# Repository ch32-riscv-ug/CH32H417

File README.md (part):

# CH32H417

<!-- This file is generated from ch32-riscv-ug/ch32-device-data (index/ + evidence/ + pipeline/build/build_readme.py). Edit there, not here. -->

[Choose a part](#product-comparison) &middot; [Documents](#documents) &middot; [Pin maps](#pin-maps--alternate-functions) &middot; [Pin viewer](https://ch32-riscv-ug.github.io/ch32-device-data/pins.html?chip=CH32H415) &middot; [Errata](#errata) &middot; [Examples](#evt-examples) &middot; [Address map](#address-map)

## Quick start

### Debug / serial defaults

Where these land **without writing a remap register**. SWD is live at reset; the UART pads are not -- the pin must still be put into alternate-function mode. See `route` in evidence/README.ja.md.

| Series | SWDIO | SWCLK | UART TX | UART RX |
|---|---|---|---|---|
| CH32H415 | PB9 | PB8 | none by default[^af] | none by default[^af] |
| CH32H416 | PB9 | PB8 | none by default[^af] | none by default[^af] |
| CH32H417 | PB9 | PB8 | none by default[^af] | none by default[^af] |

[^af]: This series selects every pin function through `AFIO->GPIOx_AFLR/AFHR` rather than through AFIO remap, so no USART is routed out until software picks one -- the pads it **can** go on are listed under Pin definitions. The reset value of `GPIOx_AFLR/AFHR` is 0, which selects AF0 (a real function, not "none"), and a pad only drives its alternate function once its GPIO mode is set to alternate.

### Datasheets and reference manual

- CH32H417DS0.PDF (datasheet): [English](https://ch32-riscv-ug.github.io/CH32H417/datasheet_en/CH32H417DS0.PDF) · [中文](https://ch32-riscv-ug.github.io/CH32H417/datasheet_zh/CH32H417DS0.PDF)
- CH32H417RM.PDF (reference manual): [English](https://ch32-riscv-ug.github.io/CH32H417/datasheet_en/CH32H417RM.PDF) · [中文](https://ch32-riscv-ug.github.io/CH32H417/datasheet_zh/CH32H417RM.PDF)

## Series

| Series | Core | ISA | Flash | SRAM | Main clock | VDD | Packages | Products | Official |
|---|---|---|---|---|---|---|---|---|---|
| **CH32H415** | QingKe V5F + QingKe V3F | RV32IMABCF + RV32IMAFCB | 960K | 896K | 160 MHz\* | - | QFN60X6 | 1 | [en](https://www.wch-ic.com/products/CH32H415.html) / [zh](https://www.wch.cn/products/CH32H415.html) |
| **CH32H416** | QingKe V5F + QingKe V3F | RV32IMABCF + RV32IMAFCB | 480K | 896K | 160 MHz\* | - | QFN60X6 | 1 | [en](https://www.wch-ic.com/products/CH32H416.html) / [zh](https://www.wch.cn/products/CH32H416.html) |
| **CH32H417** | QingKe V5F + QingKe V3F | RV32IMABCF + RV32IMAFCB | 960K | 896K | 160 MHz\* | - | QFN128,QFN68,QFN88 | 3 | [en](https://www.wch-ic.com/products/CH32H417.html) / [zh](https://www.wch.cn/products/CH32H417.html) |

\* the datasheet states no nominal system main frequency for this series, so the figure is the electrical maximum (HCLK) from the characteristics table -- a limit, not a rating.

## Product comparison

### CH32H417 product comparison

Only the 15 rows that differ between these 3 products; the other 32 are the same for all of them.

| | [CH32H417&#8203;MEU6](https://ch32-riscv-ug.github.io/ch32-device-data/pins.html?chip=CH32H417MEU6)&#8203;(QFN88) | [CH32H417&#8203;QEU6](https://ch32-riscv-ug.github.io/ch32-device-data/pins.html?chip=CH32H417QEU6)&#8203;(QFN128) | [CH32H417&#8203;WEU6](https://ch32-riscv-ug.github.io/ch32-device-data/pins.html?chip=CH32H417WEU6)&#8203;(QFN68) |
|---|---|---|---|
| **GPIO** | 65 | 95 | 50 |
| ADC/TKey Channels | 9+2 | 16+2 | 7+2 |
| HSADC Channels | 4 | 7 | 4 |
| DAC (Unit) | 2 | 2 | 1 (DAC2) |
| OPA | 2(OPA1/3) | 3 | 1(OPA1) |
| USART | 8 | 8 | 7 |
| SPI/I2S | 4/2 | 4/2 | 3/2 |
| QSPI | 1 (QSPI2) | 2 | 1 (QSPI2) |
| UHSIF | 1 | 1 | 1(1) |
| SDIO | - | 1 | - |
| USBFS/OTG_FS | 1 | 1 | - |
| USBPD Type-C | 1 | 1 | - |
| FSMC | 1(2) | 1 | 1(2) |
| SerDes | 1 | 1 | - |
| SDRAM | 1 | 1 | 1(3) |

<details><summary>All 47 rows</summary>

| | [CH32H417&#8203;MEU6](https://ch32-riscv-ug.github.io/ch32-device-data/pins.html?chip=CH32H417MEU6)&#8203;(QFN88) | [CH32H417&#8203;QEU6](https://ch32-riscv-ug.github.io/ch32-device-data/pins.html?chip=CH32H417QEU6)&#8203;(QFN128) | [CH32H417&#8203;WEU6](https://ch32-riscv-ug.github.io/ch32-device-data/pins.html?chip=CH32H417WEU6)&#8203;(QFN68) |
|---|---|---|---|
| **Flash** | 960K | 960K | 960K |
| **SRAM** | 896K | 896K | 896K |
| **GPIO** | 65 | 95 | 50 |
| **Temperature** | -40..85C | -40..85C | -40..85C |
| Core 1 HS ITCM | 128KB | 128KB | 128KB |
| Core 1 HS DTCM | 256KB | 256KB | 256KB |
| SRAM Shared code and data area | 512KB | 512KB | 512KB |
| ADTM (16-bit) | 2 | 2 | 2 |
| GPTM (16-bit) | 4 | 4 | 4 |
| GPTM (32-bit) | 4 | 4 | 4 |
| Basic (16-bit) | 2 | 2 | 2 |
| LPTIM | 2 | 2 | 2 |
| Timer Watchdog | WWDG+IWDG | WWDG+IWDG | WWDG+IWDG |
| SysTick 32-bit | 2 | 2 | 2 |
| RTC | √ | √ | √ |
| ADC/TKey Units | 2 | 2 | 2 |
| ADC/TKey Channels | 9+2 | 16+2 | 7+2 |
| HSADC Units | 1 | 1 | 1 |
| HSADC Channels | 4 | 7 | 4 |
| DAC (Unit) | 2 | 2 | 1 (DAC2) |
| OPA | 2(OPA1/3) | 3 | 1(OPA1) |
| CMP | 1 | 1 | 1 |
| DFSDM | 1 | 1 | 1 |
| RNG | 1 | 1 | 1 |
| LTDC | 1 | 1 | 1 |
| GPHA | 1 | 1 | 1 |
| DVP | 1 | 1 | 1 |
| USART | 8 | 8 | 7 |
| SPI/I2S | 4/2 | 4/2 | 3/2 |
| QSPI | 1 (QSPI2) | 2 | 1 (QSPI2) |
| I2C | 4 | 4 | 4 |
| I3C | 1 | 1 | 1 |
| UHSIF | 1 | 1 | 1(1) |
| CAN | 3 | 3 | 3 |
| SDMMC | 1 | 1 | 1 |
| SDIO | - | 1 | - |
| SAI | 1 | 1 | 1 |
| SWPMI | 1 | 1 | 1 |
| USBFS/OTG_FS | 1 | 1 | - |
| USBHS (USB2.0) | 1 | 1 | 1 |
| USBSS (USB3.0) | 1 | 1 | 1 |
| Ethernet | MAC+10/100M PHY | MAC+10/100M PHY | MAC+10/100M PHY |
| USBPD Type-C | 1 | 1 | - |
| FSMC | 1(2) | 1 | 1(2) |
| SerDes | 1 | 1 | - |
| SDRAM | 1 | 1 | 1(3) |
| PIOC | 1 | 1 | 1 |

</details>

## Block diagrams

### CH32H415

<details><summary>Internal block diagram (datasheet)</summary>

</details>

### CH32H416

<details><summary>Internal block diagram (datasheet)</summary>

</details>

### CH32H417

System block diagram from the [WCH product page](https://www.wch-ic.com/products/CH32H417.html).

<details><summary>Internal block diagram (datasheet)</summary>

</details>

## Documents

| Document | Kind | English | 中文 |
|---|---|---|---|
| CH32H417DS0.PDF | datasheet | [page](https://www.wch-ic.com/downloads/CH32H417DS0_PDF.html) [mirror](https://ch32-riscv-ug.github.io/CH32H417/datasheet_en/CH32H417DS0.PDF) v1.9 | [page](https://www.wch.cn/downloads/CH32H417DS0_PDF.html) [mirror](https://ch32-riscv-ug.github.io/CH32H417/datasheet_zh/CH32H417DS0.PDF) v1.9 |
| CH32H417RM.PDF | reference-manual | [page](https://www.wch-ic.com/downloads/CH32H417RM_PDF.html) [mirror](https://ch32-riscv-ug.github.io/CH32H417/datasheet_en/CH32H417RM.PDF) v1.8 | [page](https://www.wch.cn/downloads/CH32H417RM_PDF.html) [mirror](https://ch32-riscv-ug.github.io/CH32H417/datasheet_zh/CH32H417RM.PDF) v1.8 |
| CH32H417EVT.ZIP | evt | [page](https://www.wch-ic.com/downloads/CH32H417EVT_ZIP.html) [mirror](https://github.com/ch32-riscv-ug/CH32H417/tree/main/EVT) v1.3 | [page](https://www.wch.cn/downloads/CH32H417EVT_ZIP.html) [mirror](https://github.com/ch32-riscv-ug/CH32H417/tree/main/EVT) v1.8 |

### Evaluation boards

- board-manual:en: [CH32H417 Evaluation Board Reference-EN.pdf](https://ch32-riscv-ug.github.io/CH32H417/EVT/PUB/CH32H417%20Evaluation%20Board%20Reference-EN.pdf)
- board-manual:zh: [CH32H417评估板说明书.pdf](https://ch32-riscv-ug.github.io/CH32H417/EVT/PUB/CH32H417%E8%AF%84%E4%BC%B0%E6%9D%BF%E8%AF%B4%E6%98%8E%E4%B9%A6.pdf)
- schematic-pdf: [CH32H417SCH.pdf](https://ch32-riscv-ug.github.io/CH32H417/EVT/PUB/CH32H417SCH.pdf)

7 board schematics under `EVT/PUB/SCHPCB/`: `CH32H415REU6-R0`, `CH32H416RDU6-R0`, `CH32H417MEU6-R0`, `CH32H417MEU6-UHSIF-R0`, `CH32H417QEU-R1`, `CH32H417QEU6-R0`, `CH32H417WEU6-R0`

## Packages & pinout drawings

Pinout drawings are in the datasheet (chapter *Pinouts*); each link opens at the page that carries the drawing:

| Package | Products | Datasheet | Outline |
|---|---|---|---|
| QFN60X6 | CH32H415REU6 | [en](https://ch32-riscv-ug.github.io/CH32H417/datasheet_en/CH32H417DS0.PDF#page=33) / [zh](https://ch32-riscv-ug.github.io/CH32H417/datasheet_zh/CH32H417DS0.PDF#page=26) | [drawing](https://raw.githubusercontent.com/ch32-riscv-ug/WCH-common/main/image/package_QFN60X6.png) |
| QFN60X6 | CH32H416RDU6 | [en](https://ch32-riscv-ug.github.io/CH32H417/datasheet_en/CH32H417DS0.PDF#page=32) / [zh](https://ch32-riscv-ug.github.io/CH32H417/datasheet_zh/CH32H417DS0.PDF#page=26) | [drawing](https://raw.githubusercontent.com/ch32-riscv-ug/WCH-common/main/image/package_QFN60X6.png) |
| QFN88 | CH32H417MEU6 | [en](https://ch32-riscv-ug.github.io/CH32H417/datasheet_en/CH32H417DS0.PDF#page=30) / [zh](https://ch32-riscv-ug.github.io/CH32H417/datasheet_zh/CH32H417DS0.PDF#page=25) | [drawing](https://raw.githubusercontent.com/ch32-riscv-ug/WCH-common/main/image/package_QFN88.png) |
| QFN128 | CH32H417QEU6 | [en](https://ch32-riscv-ug.github.io/CH32H417/datasheet_en/CH32H417DS0.PDF#page=29) / [zh](https://ch32-riscv-ug.github.io/CH32H417/datasheet_zh/CH32H417DS0.PDF#page=24) | [drawing](https://raw.githubusercontent.com/ch32-riscv-ug/WCH-common/main/image/package_QFN128.png) |
| QFN68 | CH32H417WEU6 | [en](https://ch32-riscv-ug.github.io/CH32H417/datasheet_en/CH32H417DS0.PDF#page=31) / [zh](https://ch32-riscv-ug.github.io/CH32H417/datasheet_zh/CH32H417DS0.PDF#page=25) | [drawing](https://raw.githubusercontent.com/ch32-riscv-ug/WCH-common/main/image/package_QFN68.png) |

## Pin maps & alternate functions

> [!NOTE]
> These are the **pin-table superset**: the datasheet prints one pad table for every product that shares a pinout, so a pad row does not mean this part has the peripheral. Use the product comparison table above for what a given part number contains.

### CH32H415 pin map

Pin functions (filterable): [ALL](https://ch32-riscv-ug.github.io/ch32-device-data/pins.html?chip=CH32H415) [ADC](https://ch32-riscv-ug.github.io/ch32-device-data/pins.html?chip=CH32H415&features=ADC) [I2C](https://ch32-riscv-ug.github.io/ch32-device-data/pins.html?chip=CH32H415&features=I2C) [SPI](https://ch32-riscv-ug.github.io/ch32-device-data/pins.html?chip=CH32H415&features=SPI) [SYS](https://ch32-riscv-ug.github.io/ch32-device-data/pins.html?chip=CH32H415&features=SYS) [TIM](https://ch32-riscv-ug.github.io/ch32-device-data/pins.html?chip=CH32H415&features=TIM) [UART](https://ch32-riscv-ug.github.io/ch32-device-data/pins.html?chip=CH32H415&features=UART) [USB](https://ch32-riscv-ug.github.io/ch32-device-data/pins.html?chip=CH32H415&features=USB)

<details><summary><b>CH32H415 pin map</b> (61 pads x 1 products)</summary>

| Pin name | Type | [CH32H415&#8203;REU6](https://ch32-riscv-ug.github.io/ch32-device-data/pins.html?chip=CH32H415REU6)&#8203;(QFN60X6) | Notes |
|---|---|---|---|
| PA0 | I/O/A | 14 |  |
| PA1 | I/O/A | 15 |  |
| PA2 | I/O/A | 16 |  |
| PA3 | I/O/A | 17 |  |
| PA4 | I/O/A | 18 |  |
| PA5 | I/O/A | 19 |  |
| PA6 | I/O/A | 20 |  |
| PA7 | I/O/A | 21 |  |
| PA9 | I/O/A | 40 |  |
| PA10 | I/O/A | 41 |  |
| PA11 | I/O/A | 42 |  |
| PA12 | I/O/A | 43 |  |
| PA13 | I/O | 44 |  |
| PA14 | I/O | 45 |  |
| PA15 | I/O | 46 |  |
| PB0 | I/O/A | 23 |  |
| PB1 | I/O/A | 24 |  |
| PB3 | I/O | 55 |  |
| PB4 | I/O | 56 |  |
| PB6 | I/O | 57 |  |
| PB7 | I/O | 58 |  |
| PB8 | I/O/A | 59 | SWCLK |
| PB9 | I/O/A | 60 | SWDIO |
| PB10 | I/O | 29 |  |
| PB11 | I/O | 30 |  |
| PB12 | I/O | 32 |  |
| PB13 | I/O | 33 |  |
| PB14 | I/O | 34 |  |
| PB15 | I/O | 35 |  |
| PC0 | I/O/A | 9 |  |
| PC1 | I/O/A | 10 |  |
| PC2 | I/O/A | 11 |  |
| PC3 | I/O/A | 12 |  |
| PC4 | I/O/A | 22 |  |
| PC6 | I/O | 36 |  |
| PC7 | I/O | 37 |  |
| PC8 | I/O | 38 |  |
| PC9 | I/O | 39 |  |
| PC10 | I/O | 47 |  |
| PC11 | I/O | 48 |  |
| PC12 | I/O | 49 |  |
| PD3 | I/O | 50 |  |
| PE0 | I/O | 54 |  |
| PE3 | I/O | 1 |  |
| PE4 | I/O | 2 |  |
| PE5 | I/O | 3 |  |
| PE6 | I/O | 4 |  |
| PE11 | I/O | 25 |  |
| PE12 | I/O | 26 |  |
| PE13 | I/O | 27 |  |
| PE14 | I/O | 28 |  |
| PE15 | I/O | 29 |  |
| PF3 | I/O | 51 |  |
| PF4 | I/O | 52 |  |
| PF5 | I/O | 53 |  |
| VDD33 | P | 6/31 |  |
| VDD33A | P | 13 |  |
| VDDK | P | 5 |  |
| VSS | P | EP |  |
| XI | I/A | 7 |  |
| XO | O/A | 8 |  |

</details>

<details><summary><b>CH32H415 alternate functions</b></summary>

| Pad | default | af-0 | af-1 | af-10 | af-11 | af-12 | af-13 | af-14 | af-15 | af-2 | af-3 | af-4 | af-5 | af-6 | af-7 | af-8 | af-9 |
|---|---|---|---|---|---|---|---|---|---|---|---|---|---|---|---|---|---|
| PA0 | ADC_IN0, OPA3_OUT0 | - | TIM2_CH1_ETR | - | - | - | - | LTDC_R0 | - | TIM5_CH1 | TIM8_ETR | QSPI2_SIOX2 | PIOC_IO0 | TIM9_CH1 | USART2_CTS | USART6_TX | SDIO_CMD |
| PA1 | ADC_IN1 | - | TIM2_CH2 | - | - | - | - | LTDC_R2 | - | TIM5_CH2 | - | QSPI2_SIOX3 | - | TIM9_CH2 | USART2_RTS | USART6_RX | QSPI1_SIO3 |
| PA2 | ADC_IN2, OPA3_P1 | - | TIM2_CH3 | - | - | - | - | LTDC_R1 | - | TIM5_CH3 | USART6_CK | TIM9_CH3 | - | - | USART2_TX | - | - |
| PA3 | ADC_IN3, OPA3_N1 | - | TIM2_CH4 | - | - | - | - | LTDC_B5 | - | TIM5_CH4 | - | TIM9_CH4 | - | - | USART2_RX | TIM10_CH3 | LTDC_B2 |
| PA4 | ADC_IN4, DAC1_OUT, OPA3_OUT1 | - | - | - | - | - | DVP_HSYNC | LTDC_VSYNC | - | TIM5_ETR | - | TIM9_ETR | SPI1_NSS | I2S3_WS, SPI3_NSS | USART2_CK | - | TIM10_CH4 |
| PA5 | ADC_IN5, DAC2_OUT, OPA1_OUT1 | - | TIM2_CH1_ETR | - | DVP_VSYNC | - | - | LTDC_R4 | - | TIM1_BKIN2 | TIM8_CH1N | - | SPI1_SCK | - | - | - | TIM10_ETR |
| PA6 | ADC_IN6, OPA1_P1 | - | TIM1_BKIN | CMP_OUT | LTDC_HSYNC | - | DVP_PCLK | LTDC_G2 | - | TIM3_CH1 | TIM8_BKIN | - | SPI1_MISO | - | - | - | TIM10_CH1 |
| PA7 | ADC_IN7, OPA1_N1 | - | TIM1_CH1N | - | - | - | - | LTDC_VSYNC | - | TIM3_CH2 | TIM8_CH1N | - | SPI1_MOSI | - | - | - | TIM10_CH2 |
| PA9 | OTG_VBUS | - | TIM1_CH2 | - | - | - | DVP_D0 | LTDC_R5 | - | - | - | I2C3_SMBA | I2S2_CK, SPI2_SCK | - | USART1_TX | - | - |
| PA10 | OTG_ID | - | TIM1_CH3 | - | - | LTDC_B4 | DVP_D1 | LTDC_B1 | - | - | - | - | - | USART6_CK | USART1_RX | - | - |
| PA11 | OTG_DM | - | TIM1_CH4 | - | - | - | - | LTDC_R4 | - | - | - | USART3_CK | I2S2_WS, SPI2_NSS | USART6_RX | USART1_CTS | - | CAN1_RX |
| PA12 | OTG_DP | - | TIM1_ETR | - | - | TIM1_BKIN2 | - | LTDC_R5 | - | - | - | USART3_RTS | I2S2_CK, SPI2_SCK | USART6_TX | USART1_RTS | - | CAN1_TX |
| PA13 | - | - | I2S3_SD, SPI3_MOSI | - | - | - | SAI_SD_B | - | - | - | - | USART3_TX | CAN_RX | - | I2C3_SDA | LTDC_B2 | - |
| PA14 | - | - | I2S3_CK, SPI3_SCK | - | USART8_CK | - | SAI_SCK_B | LTDC_B6 | LTDC_R0 | - | - | USART3_RX | CAN_TX | - | I2C3_SCL | - | - |
| PA15 | - | - | TIM2_CH1_ETR | LTDC_B4 | USART8_TX | - | SAI_FS_B | LTDC_B6 | LTDC_CLK | - | - | USART3_CTS | SPI1_NSS | I2S3_WS, SPI3_NSS | I2C3_SMBA | USART6_RTS | LTDC_R3 |
| PB0 | ADC_IN8, CMP_P0, OPA1_P0 | MCO | TIM1_CH2N | - | - | - | TIM12_ETR | LTDC_G1 | - | TIM3_CH3 | TIM8_CH2N | TIM5_CH4 | - | DFSDM_CKOUT | - | USART6_CTS | LTDC_R3 |
| PB1 | ADC_IN9, CMP_N0, OPA1_N0 | - | TIM1_CH3N | - | - | - | - | LTDC_G0 | - | TIM3_CH4 | TIM8_CH3N | - | TIM12_CH1 | DFSDM_DATIN1 | - | - | LTDC_R6 |
| PB3 | - | - | TIM2_CH2 | - | USART8_RX | - | DVP_D5 | TIM12_ETR | - | - | - | CC1 | SPI1_SCK | I2S3_CK, SPI3_SCK | - | - | SDIO_D2 |
| PB4 | - | - | - | TIM4_ETR | USART8_TX | - | - | USART7_CK | - | TIM3_CH1 | - | CC2 | SPI1_MISO | SPI3_MISO | I2S2_WS, SPI2_NSS | - | SDIO_D3 |
| PB6 | - | TIM10_CH1 | - | QSPI1_SCSN | - | - | DVP_D5 | USART7_TX | - | TIM4_CH1 | CAN1_RX | I2C1_SCL | I2S3_MCK | I2C4_SCL | USART1_TX | - | CAN2_TX |
| PB7 | - | TIM10_CH2 | - | USART8_CK | - | - | DVP_VSYNC | - | - | TIM4_CH2 | CAN1_TX | I2C1_SDA | - | I2C4_SDA | USART1_RX | - | - |
| PB8 | SWCLK, USBHS_DP | - | TIM10_CH3 | SDIO_D4 | - | - | DVP_D6 | LTDC_B6 | - | TIM4_CH3 | - | I2C1_SCL | PIOC_IO0 | I2C4_SCL | - | USART6_RX | CAN1_RX |
| PB9 | SWDIO, SWIO, USBHS_DM | - | TIM10_CH4 | SDIO_D5 | I2C4_SMBA | - | DVP_D7 | LTDC_B7 | - | TIM4_CH4 | - | I2C1_SDA | I2S2_WS, SPI2_NSS | I2C4_SDA | PIOC_IO1 | USART6_TX | CAN1_TX |
| PB10 | - | - | TIM2_CH3 | - | QSPI2_SCSXN | - | - | LTDC_G4 | - | TIM9_CH2 | LPTIM2_CH1 | I2C2_SCL | I2S2_CK, SPI2_SCK | - | USART3_TX | SDIO_CMD | USART6_CK |
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
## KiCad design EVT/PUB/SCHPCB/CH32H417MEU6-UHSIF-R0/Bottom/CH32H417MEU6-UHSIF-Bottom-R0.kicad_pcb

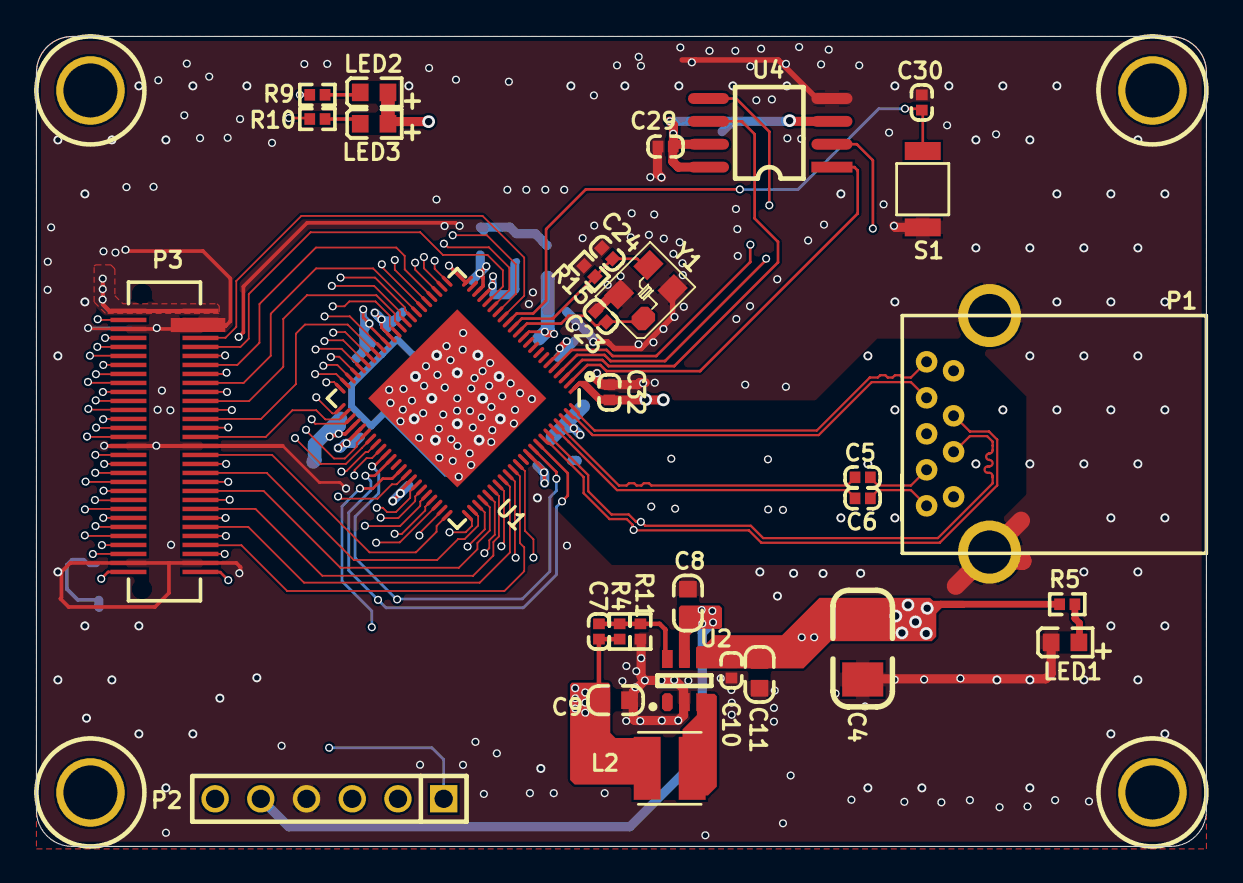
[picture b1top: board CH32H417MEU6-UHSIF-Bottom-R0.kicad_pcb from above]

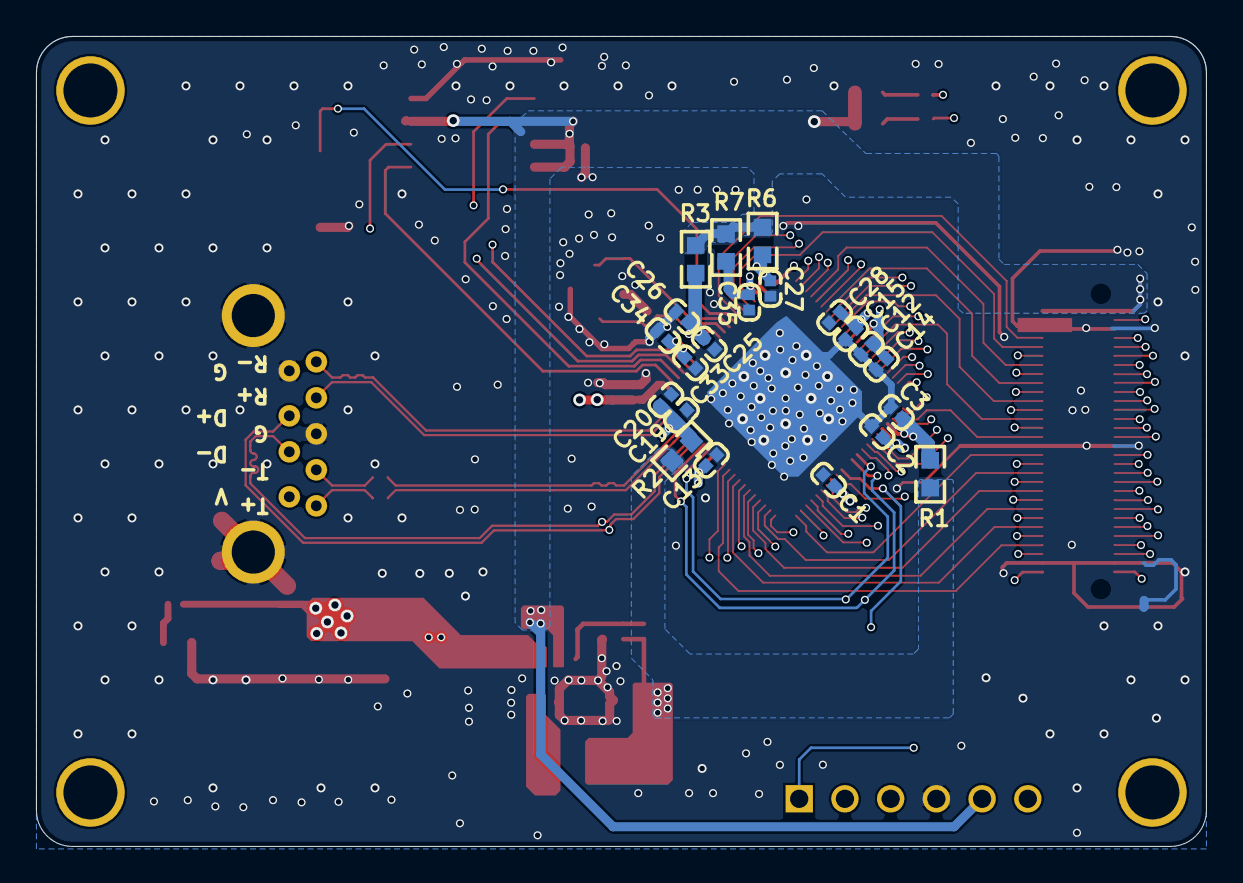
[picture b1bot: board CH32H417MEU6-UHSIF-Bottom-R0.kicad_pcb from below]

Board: 4 copper layers, 65.0 x 45.0 mm, 52 parts (21 on the bottom side), 84 nets.

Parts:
C1, C2, C3, C5, C6, C12, C13, C15, C19, C25, C27, C29, C30, C32, C33, C35: 0.1uF; 0402_C
C4: 47uF; 3528_C
C7: NC(4.7pF); 0402_C
C8, C9, C11: 10uF; 0603_C
C10: 1uF; 0402_C
C14, C26: 10uF; 0402_C
C20, C28, C34: 2.2uF; 0402_C
C23, C24: 20pF; 0402_C
L2: 2.2uH; CD32
LED1: RED; 0603+
LED2: BLUE; 0603+
LED3: GREEN; 0603+
P1: USB3.0-A; USB3.0-A-RECEPTACLE
P2: HEADER 6; SIP6-2.54mm
P3: HEADER 30x2; BTB-60P-P0.5-MR
R1, R2, R3, R6, R7: 0R; 0603
R4: 0Ω; 0402
R5: 1K; 0402
R9, R10: 470Ω; 0402
R11: NC(200k); 0402
R15: NC; 0402
S1: 贴片按键
U1: CH32H417MEU6; QFN88_10X10
U2: CH2003V; SOT-23-6
U4: SPI FLASH; SOIC-8_208mil
Y1: 25M; XT3225

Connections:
1V2: C7.1, C9.2, L2.2, R1.2, R2.2, R4.1
3V3: C8.2, C29.2, LED2.1, LED3.1, P2.5, P3.1, P3.2, R3.2, R6.2, R7.2, U2.5, U4.3, U4.7, U4.8
+5V: C4.1, C10.2, C11.2, P1.1, P2.6, R5.2, U2.4
GND: C1.2, C2.2, C3.1, C4.2, C8.1, C9.1, C10.1, C11.1, C12.2, C13.2, C14.2, C15.1, C19.1, C20.1, C23.1, C24.1, C25.1, C26.1, C27.1, C28.1, C29.1, C30.1, C32.1, C33.1, C34.1, C35.1, LED1.2, P1.0, P1.4, P1.7, P2.4, P3.4, P3.5, P3.6, P3.31, P3.32, P3.57, P3.58, R11.2, R15.1, S1.2, U1.0, U2.2, U4.4, Y1.2, Y1.4
LED1: R9.1, U1.22
LED2: R10.1, U1.23
NRST: C30.2, S1.1, U1.14
NetC5_2: C5.2, P1.8
NetC6_2: C6.2, P1.9
NetC7_2: C7.2, R4.2, R11.1, U2.6
NetL2_1: L2.1, U2.3
NetLED1_1: LED1.1, R5.1
NetLED2_2: LED2.2, R9.2
NetLED3_2: LED3.2, R10.2
RX1: P3.60, U1.55, U1.81
RX8: P3.59, U1.54, U1.80
SPI_CS: U1.2, U4.1
SPI_MISO: U1.4, U4.2
SPI_MOSI: U1.5, U4.5
SPI_SCK: U1.3, U4.6
SWCLK: P1.3, P2.2, U1.82
SWDIO: P1.2, P2.3, U1.83
TX6: P2.1, U1.57
UFP0: P3.3, U1.16
UFP1: P3.7, U1.17
UFP2: P3.10, U1.18
UFP3: P3.9, U1.24
UFP4: P3.12, U1.25
UFP5: P3.14, U1.26
UFP6: P3.11, U1.27
UFP7: P3.13, U1.28
UFP8: P3.18, U1.29
UFP9: P3.15, U1.30
UFP10: P3.16, U1.31
UFP11: P3.22, U1.32
UFP12: P3.17, U1.33
UFP13: P3.19, U1.36
UFP14: P3.26, U1.37
UFP15: P3.21, U1.38
UFP16: P3.20, U1.39
UFP17: P3.25, U1.40
UFP18: P3.23, U1.41
UFP19: P3.24, U1.42
UFP20: P3.27, U1.43
UFP21: P3.28, U1.44
UFP22: P3.29, U1.45
UFP23: P3.30, U1.46
UFP24: P3.33, U1.47
UFP25: P3.35, U1.50
UFP26: P3.37, U1.51
UFP27: P3.39, U1.52
UFP28: P3.41, U1.53
UFP29: P3.43, U1.58
UFP30: P3.45, U1.60
UFP31: P3.47, U1.61
UFP32: P3.49, U1.62
UFP33: P3.51, U1.63
UFP34: P3.53, U1.64
UFP35: P3.55, U1.65
UFP36: P3.34, U1.66
UFP37: P3.36, U1.67
UFP38: P3.38, U1.68
UFP39: P3.40, U1.69
UFP40: P3.42, U1.70
UFP41: P3.44, U1.71
UFP42: P3.46, U1.72
UFP43: P3.48, U1.73
UFP44: P3.50, U1.74
UFP45: P3.52, U1.75
UFP46: P3.54, U1.76
UFP47: P3.56, U1.77
UFPCLK: P3.8, U1.15
USB_SSRX_n: P1.6, U1.87
USB_SSRX_p: P1.5, U1.88
USB_SSTX_n: C6.1, U1.84
USB_SSTX_p: C5.1, U1.85
VDD12A: C19.2, C20.2, R2.1, U1.86
VDD33: C1.1, C25.2, C26.2, C32.2, R3.1, U1.1, U1.11, U1.59
VDD33A: C27.2, R6.1, U1.20
VDDIO: C12.1, C14.1, C35.2, R7.1, U1.19, U1.35
VDDK: C3.2, C33.2, C34.2, R1.1, U1.6, U1.48
VIO18: C2.1, C13.1, C15.2, C28.2, U1.34, U1.49, U1.79
XI: C23.2, U1.12, Y1.1
XO: C24.2, R15.2, U1.13, Y1.3

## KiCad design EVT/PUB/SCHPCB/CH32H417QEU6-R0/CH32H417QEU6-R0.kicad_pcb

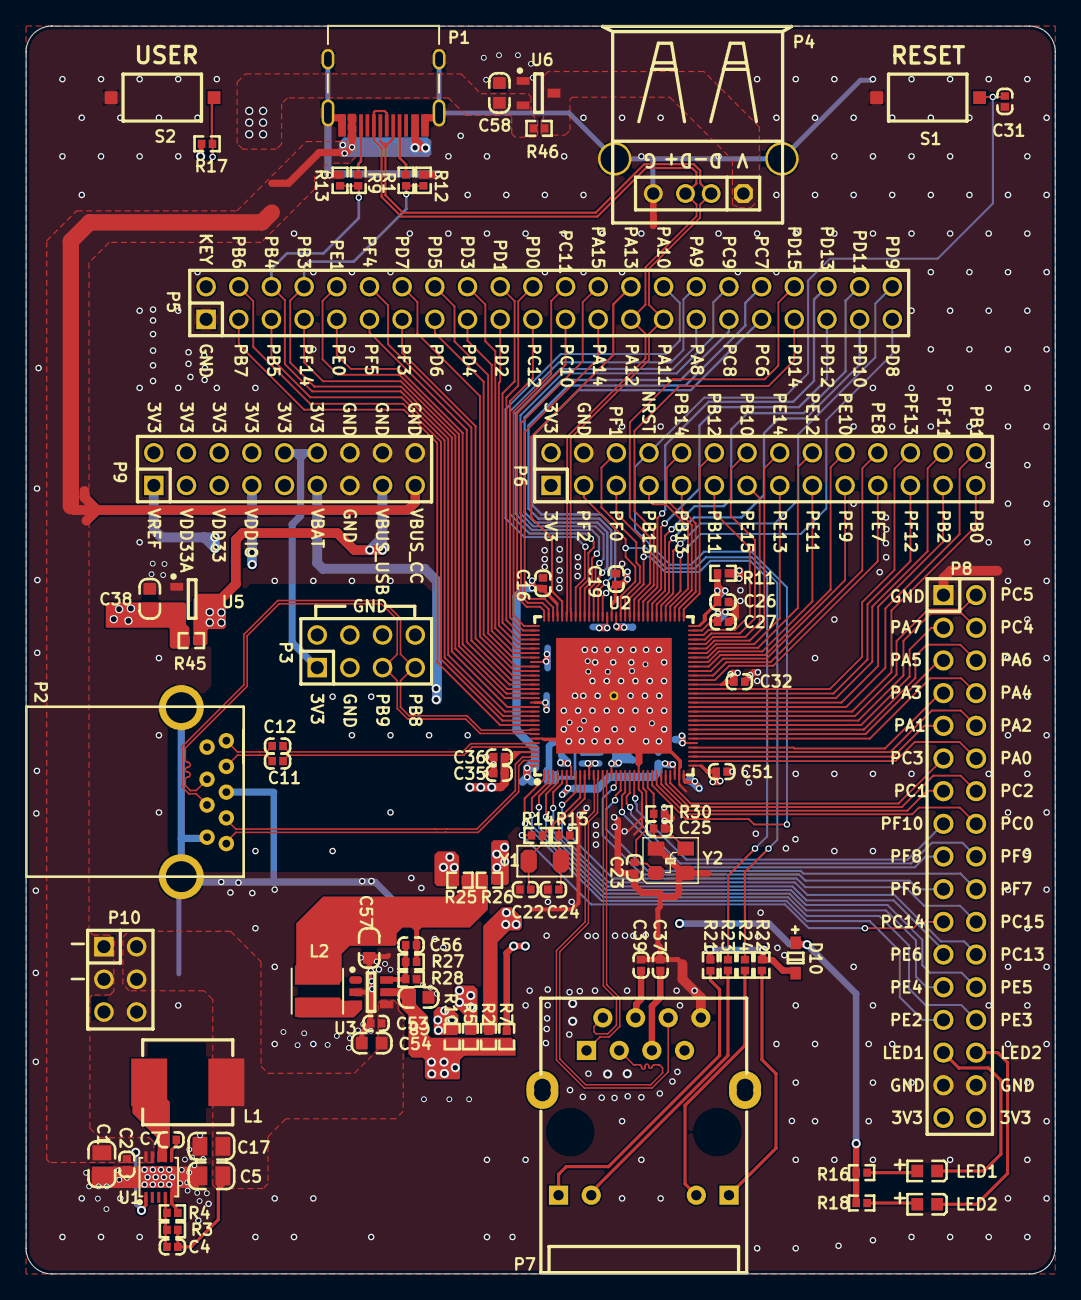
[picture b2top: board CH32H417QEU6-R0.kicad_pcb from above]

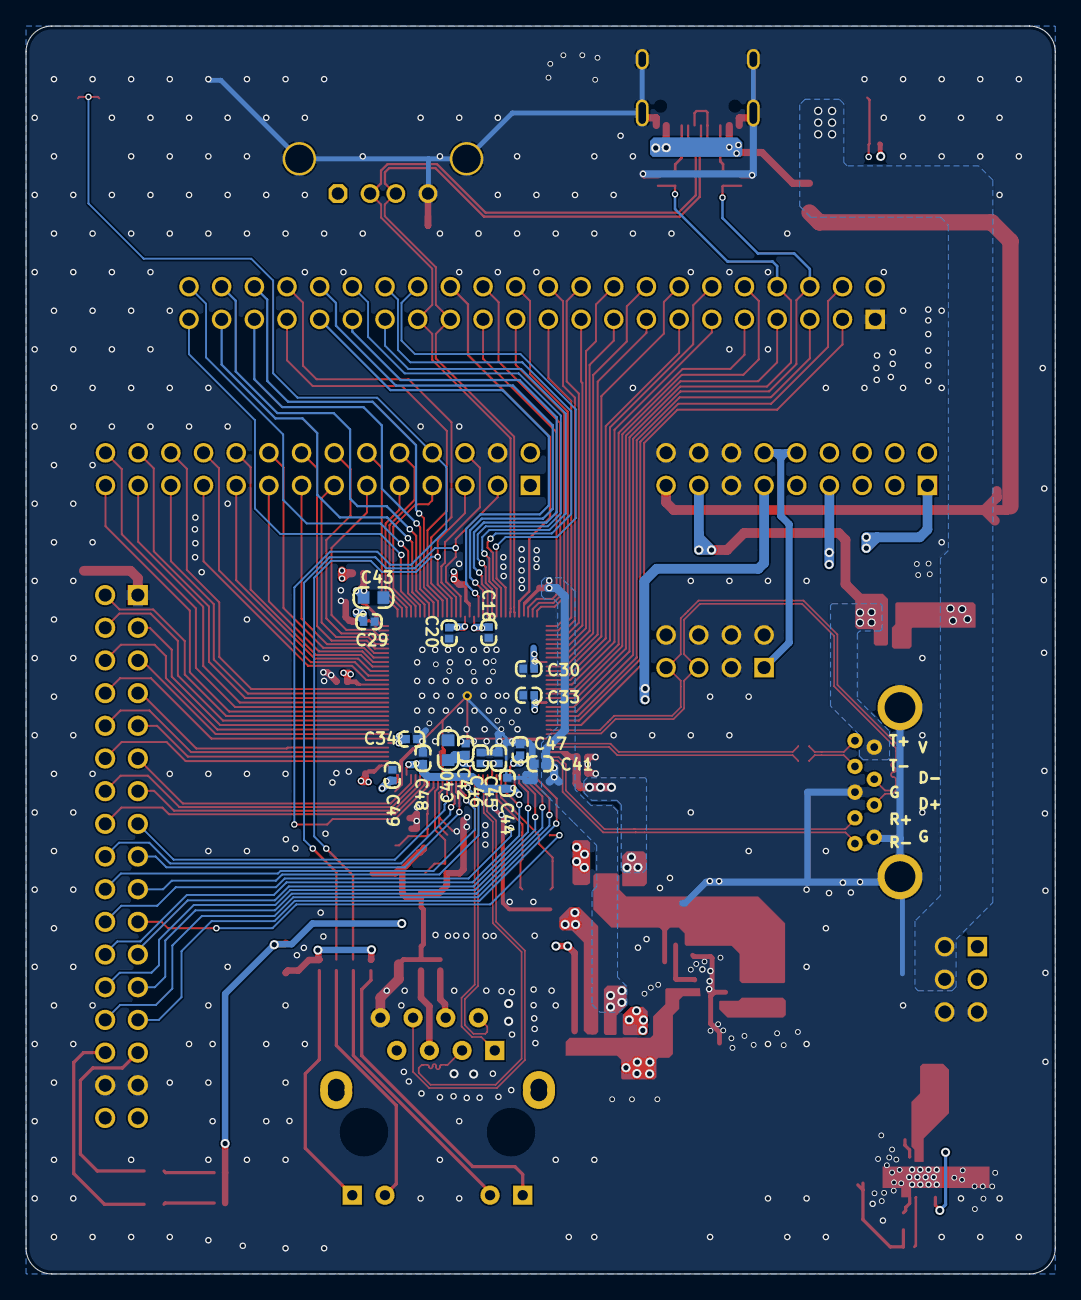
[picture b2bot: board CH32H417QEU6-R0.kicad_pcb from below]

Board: 4 copper layers, 80.0 x 97.0 mm, 97 parts (16 on the bottom side), 144 nets.

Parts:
C1: NC(22uF/35V); 0805_C
C2: NC(0.1uF); 0402_C
C4: NC(68pF); 0402_C
C5, C17: NC(22uF); 0805_C
C7: NC(100nF); 0402_C
C8, C38, C40, C43, C54, C58: 10uF; 0603_C
C11, C12, C16, C18, C19, C20, C26, C27, C30, C31, C32, C33, C34, C36, C37, C39, C41, C42, C44, C45, C47, C48, C49, C51: 0.1uF; 0402_C
C22, C24: 12pF; 0402_C
C23, C25: 18pF; 0402_C
C29, C35, C46: 2.2uF; 0402_C
C53: 1uF; 0402_C
C56: NC(4.7pF); 0402_C
C57: NC(10uF); 0603_C
D10: Diode; SOD-323
L1: NC(4.7uH/5A); IND-SMD_L7.0-W6.6
L2: NC(2.2uH); CD32
LED1: LED2 blue; 0603+
LED2: LED1 blue; 0603+
P1: TYPE-C; TYPE-C-Receptacle-2.0
P2: USB3.0-A; USB3.0-A-Receptacle
P3: HEADER 4x2; IDC8-2.54mm
P4: USB_A; USBAF
P5: IDC44-2.54MM
P6: HEADER 14x2; IDC28-2.54MM
P7: HR911105A
P8: HEADER 17x2; IDC34-2.54MM
P9: HEADER 9x2; IDC18-2.54MM
P10: HEADER 3x2; IDC6-2.54mm
R1, R2, R5, R7, R9, R10, R23, R24: 0Ω; 0402
R3: NC(15K); 0402
R4: NC(4.7K); 0402
R11, R14, R15, R25, R26, R27, R45, R46: NC(0Ω); 0402
R12, R13: NC(5.1K); 0402
R16, R18, R21, R22: 1k; 0402
R17: 10K; 0402
R28: NC(200K); 0402
R30: 100K(NC); 0402
S1: RESET; SMD_6.1x3.65x2.5mm-KEY
S2: USER; SMD_6.1x3.65x2.5mm-KEY
U1: NC(CH2024Q); DFN10_3X3
U2: CH32H417QEU6; QFN128_12.3X12.3
U3: CH2003V; SOT-23-6
U5, U6: CH213; SOT-23-3
Y1: 32.768k; FC-135
Y2: 25M; XT3225

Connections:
1V2: C56.1, C57.2, L2.2, R25.2, R26.2, R27.1
3V3: C8.2, P3.1, P6.1, P6.2, P8.33, P8.34, P9.2, P9.4, P9.6, P9.8, P9.10, P9.12, R2.2, R5.2, R7.2, R10.2, R17.1, U3.5
5V: C4.1, C5.2, C17.2, C38.1, C53.2, C54.2, C58.1, L1.2, P10.2, P10.4, R3.2, R45.1, R46.1, U3.4, U5.2, U6.2
CC1: P5.8, R1.1, R12.1, U2.115
CC1_1: P1.A5, R1.2
CC1_2: P1.B5, R9.2
CC2: P5.6, R9.1, R13.1, U2.116
ELED0: P7.11, R24.2
ELED1: P7.10, R23.2
FB: C4.2, R3.1, R4.2, U1.4
GND: C1.1, C2.1, C5.1, C8.1, C16.2, C17.1, C18.2, C19.2, C20.2, C22.2, C23.1, C24.2, C25.1, C26.2, C27.2, C29.1, C30.2, C31.1, C32.2, C33.1, C34.1, C35.1, C36.1, C37.1, C38.2, C39.1, C40.1, C41.1, C42.1, C43.1, C44.1, C45.1, C46.2, C47.1, C48.2, C49.1, C51.1, C53.1, C54.1, C57.1, C58.2, P1.0, P1.A1, P1.B1, P2.0, P2.4, P2.7, P3.2, P3.3, P3.4, P3.6, P3.8, P4.0, P4.4, P5.1, P6.4, P7.8, P8.1, P8.31, P8.32, P9.13, P9.14, P9.16, P9.18, P10.5, P10.6, R4.1, R12.2, R13.2, R28.2, R30.1, S1.2, S2.2, U1.0, U1.5, U2.0, U2.22, U2.31, U2.122, U3.2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
KEY: P5.2, R17.2, S2.1
LED1: LED1.2, P8.29
LED2: LED2.2, P8.30
MDIRN: P7.6, U2.12
MDIRP: P7.3, U2.13
MDITN: P7.2, U2.14
MDITP: P7.1, U2.15
NRST: C31.2, P6.8, S1.1, U2.25
NetC7_1: C7.1, U1.6
NetC7_2: C7.2, L1.1, U1.7, U1.8
NetC11_1: C11.1, P2.8
NetC12_1: C12.1, P2.9
NetC37_2: C37.2, P7.5
NetC39_2: C39.2, P7.4
NetC56_2: C56.2, R27.2, R28.1, U3.6
NetD10_2: D10.2, R21.1, R22.1
NetL2_1: L2.1, U3.3
NetLED1_1: LED1.1, R16.2
NetLED2_1: LED2.1, R18.2
NetP7_9: P7.9, R21.2
NetP7_12: P7.12, R22.2
OTG_FS_DM: P1.A7, P1.B7, P4.2, P5.29, U2.90
OTG_FS_DP: P1.A6, P1.B6, P4.3, P5.27, U2.91
PA0: P8.12, U2.34
PA1: P8.9, U2.35
PA2: P8.10, U2.36
PA3: P8.7, U2.37
PA4: P8.8, U2.39
PA5: P8.5, U2.40
PA6: P8.6, U2.41
PA7: P8.3, U2.42
PA8: P5.31, U2.87
PA9: P5.32, U2.88
PA10: P5.30, U2.89
PA13: P5.28, U2.92
PA14: P5.25, U2.94
PA15: P5.26, U2.95
PB0: P6.27, U2.45
PB1: P6.28, U2.46
PB2: P6.25, U2.47
PB5: P5.5, U2.117
PB6: P5.4, U2.118
PB7: P5.3, U2.119
PB8: P2.3, P3.7, U2.120
PB9: P2.2, P3.5, U2.121
PB10: P6.14, U2.61
PB11: P6.11, U2.62
PB12: P6.12, U2.65
PB13: P6.9, U2.66
PB14: P6.10, U2.67
PB15: P6.7, U2.68
PC0: P8.16, U2.26
PC1: P8.13, U2.27
PC2: P8.14, U2.28
PC3: P8.11, U2.29
PC4: P8.4, U2.43
PC5: P8.2, U2.44
PC6: P5.35, U2.83
PC7: P5.36, U2.84
PC8: P5.33, U2.85
PC9: P5.34, U2.86
PC10: P5.23, U2.96
PC11: P5.24, U2.97
PC12: P5.21, U2.98
PC13: P8.24, U2.8
PC14: P8.21, R14.1
PC15: P8.22, R15.1
PD0: P5.22, U2.99
PD1: P5.20, U2.100
PD2: P5.19, U2.101
PD3: P5.18, U2.102
PD4: P5.17, U2.103
PD5: P5.16, U2.104
PD6: P5.15, U2.106
PD7: P5.14, U2.107
PD8: P5.43, U2.69
PD9: P5.44, U2.70
PD10: P5.41, U2.71
PD11: P5.42, U2.72
PD12: P5.39, U2.73
PD13: P5.40, U2.74
PD14: P5.37, U2.75
PD15: P5.38, U2.76
PE0: P5.9, U2.111
PE1: P5.10, U2.112
PE2: P8.27, U2.1
PE3: P8.28, U2.2
PE4: P8.25, U2.3
PE5: P8.26, U2.4
PE6: P8.23, U2.5
PE7: P6.21, U2.52
PE8: P6.22, U2.53
PE9: P6.19, U2.54
PE10: P6.20, U2.55
PE11: P6.17, U2.56
PE12: P6.18, U2.57
PE13: P6.15, U2.58
PE14: P6.16, U2.59
PE15: P6.13, U2.60
PF0: P6.5, R23.1, U2.77
PF1: P6.6, U2.78
PF2: P6.3, R24.1, U2.79
PF3: P5.13, U2.108
PF4: P5.12, U2.109
PF5: P5.11, U2.110
PF6: P8.19, U2.17
PF7: P8.20, U2.18
PF8: P8.17, U2.19
PF9: P8.18, U2.20
PF10: P8.15, U2.21
PF11: P6.26, U2.48
PF12: P6.23, U2.49
PF13: P6.24, U2.50
PF14: P5.7, U2.113
USBSS_RXN: P2.6, U2.126
USBSS_RXP: P2.5, U2.127
USBSS_TXN: C12.2, U2.123
USBSS_TXP: C11.2, U2.124
VBAT: C47.2, P9.11, U2.7
VBUS_CC: C1.2, C2.2, P1.A4, P1.B4, P9.17, P10.1, P10.3, U1.1, U1.9, U1.10
VBUS_FS: P4.1, R46.2, U6.3
VBUS_USB: P2.1, P9.15, R45.2, U5.3
VDD33: C16.1, C40.2, C41.2, C42.2, P9.5, R5.1, U2.16, U2.93, U2.128
VDD33A: C51.2, P9.3, R10.1, U2.33
VDDIO: C18.1, C26.1, C32.1, C33.2, C34.2, C43.2, C44.2, C48.1, D10.1, P9.7, R2.1, R11.2, R16.1, R18.1, U2.6, U2.30, U2.38, U2.51, U2.64, U2.82, U2.114
VDDK: C20.1, C45.2, C46.1, R26.1, U2.11, U2.80
VDD_1.2A: C35.2, C36.2, R25.1, U2.125
VIO_1.8: C19.1, C27.1, C29.2, C30.1, P9.9, R11.1, U2.63, U2.81, U2.105
VREF: C49.2, P9.1, R7.1, U2.32
X32KI: C22.1, R14.2, U2.9, Y1.1
X32KO: C24.1, R15.2, U2.10, Y1.2
XI: C23.2, U2.23, Y2.1
XO: C25.2, R30.2, U2.24, Y2.3

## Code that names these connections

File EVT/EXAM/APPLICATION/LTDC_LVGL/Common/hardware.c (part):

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    RCC_HB2PeriphClockCmd(RCC_HB2Periph_GPIOE, ENABLE);
    RCC_HB2PeriphClockCmd(RCC_HB2Periph_GPIOF, ENABLE);

    // CLK PF1(AF14)
    GPIO_PinAFConfig(GPIOF, GPIO_PinSource1, GPIO_AF14);
    GPIO_InitStructure.GPIO_Pin   = GPIO_Pin_1;
    GPIO_InitStructure.GPIO_Speed = GPIO_Speed_Very_High;
    GPIO_InitStructure.GPIO_Mode  = GPIO_Mode_AF_PP;
    GPIO_Init(GPIOF, &GPIO_InitStructure);

    // HSYNC PC6(AF14)
    GPIO_PinAFConfig(GPIOC, GPIO_PinSource6, GPIO_AF14);
    GPIO_InitStructure.GPIO_Pin   = GPIO_Pin_6;
    GPIO_InitStructure.GPIO_Speed = GPIO_Speed_Very_High;
    GPIO_InitStructure.GPIO_Mode  = GPIO_Mode_AF_PP;
    GPIO_Init(GPIOC, &GPIO_InitStructure);

    // VSYNC PA7(AF14)
    GPIO_PinAFConfig(GPIOA, GPIO_PinSource7, GPIO_AF14);
    GPIO_InitStructure.GPIO_Pin   = GPIO_Pin_7;
    GPIO_InitStructure.GPIO_Speed = GPIO_Speed_Very_High;
    GPIO_InitStructure.GPIO_Mode  = GPIO_Mode_AF_PP;
    GPIO_Init(GPIOA, &GPIO_InitStructure);

    // DE PC5(AF14)
    GPIO_PinAFConfig(GPIOC, GPIO_PinSource5, GPIO_AF14);
    GPIO_InitStructure.GPIO_Pin   = GPIO_Pin_5;
    GPIO_InitStructure.GPIO_Speed = GPIO_Speed_Very_High;
    GPIO_InitStructure.GPIO_Mode  = GPIO_Mode_AF_PP;
    GPIO_Init(GPIOC, &GPIO_InitStructure);

    // R[0] PE1(AF14)
    GPIO_PinAFConfig(GPIOE, GPIO_PinSource1, GPIO_AF14);
    GPIO_InitStructure.GPIO_Pin   = GPIO_Pin_1;
    GPIO_InitStructure.GPIO_Speed = GPIO_Speed_Very_High;
    GPIO_InitStructure.GPIO_Mode  = GPIO_Mode_AF_PP;
    GPIO_Init(GPIOE, &GPIO_InitStructure);

    // R[1] PF0(AF11)
    GPIO_PinAFConfig(GPIOF, GPIO_PinSource0, GPIO_AF11);
    GPIO_InitStructure.GPIO_Pin   = GPIO_Pin_0;
    GPIO_InitStructure.GPIO_Speed = GPIO_Speed_Very_High;
    GPIO_InitStructure.GPIO_Mode  = GPIO_Mode_AF_PP;
    GPIO_Init(GPIOF, &GPIO_InitStructure);

    // R[2] PD13(AF3)
    GPIO_PinAFConfig(GPIOD, GPIO_PinSource13, GPIO_AF3);
    GPIO_InitStructure.GPIO_Pin   = GPIO_Pin_13;
    GPIO_InitStructure.GPIO_Speed = GPIO_Speed_Very_High;
    GPIO_InitStructure.GPIO_Mode  = GPIO_Mode_AF_PP;
    GPIO_Init(GPIOD, &GPIO_InitStructure);

    // R[3] PD12(AF11)
    GPIO_PinAFConfig(GPIOD, GPIO_PinSource12, GPIO_AF11);
    GPIO_InitStructure.GPIO_Pin   = GPIO_Pin_12;
    GPIO_InitStructure.GPIO_Speed = GPIO_Speed_Very_High;
    GPIO_InitStructure.GPIO_Mode  = GPIO_Mode_AF_PP;
    GPIO_Init(GPIOD, &GPIO_InitStructure);

    // R[4] PD11(AF11)
    GPIO_PinAFConfig(GPIOD, GPIO_PinSource11, GPIO_AF11);
    GPIO_InitStructure.GPIO_Pin   = GPIO_Pin_11;
    GPIO_InitStructure.GPIO_Speed = GPIO_Speed_Very_High;
    GPIO_InitStructure.GPIO_Mode  = GPIO_Mode_AF_PP;
    GPIO_Init(GPIOD, &GPIO_InitStructure);

    // R[5] PA9(AF14)
    GPIO_PinAFConfig(GPIOA, GPIO_PinSource9, GPIO_AF14);
    GPIO_InitStructure.GPIO_Pin   = GPIO_Pin_9;
    GPIO_InitStructure.GPIO_Speed = GPIO_Speed_Very_High;
    GPIO_InitStructure.GPIO_Mode  = GPIO_Mode_AF_PP;
    GPIO_Init(GPIOA, &GPIO_InitStructure);

    // R[6] PA8(AF14)
    GPIO_PinAFConfig(GPIOA, GPIO_PinSource8, GPIO_AF14);
    GPIO_InitStructure.GPIO_Pin   = GPIO_Pin_8;
    GPIO_InitStructure.GPIO_Speed = GPIO_Speed_Very_High;
    GPIO_InitStructure.GPIO_Mode  = GPIO_Mode_AF_PP;
    GPIO_Init(GPIOA, &GPIO_InitStructure);

    // R[7] PC4(AF14)
    GPIO_PinAFConfig(GPIOC, GPIO_PinSource4, GPIO_AF14);
    GPIO_InitStructure.GPIO_Pin   = GPIO_Pin_4;
    GPIO_InitStructure.GPIO_Speed = GPIO_Speed_Very_High;
    GPIO_InitStructure.GPIO_Mode  = GPIO_Mode_AF_PP;
    GPIO_Init(GPIOC, &GPIO_InitStructure);

    // G[0] PE5(AF14)
    GPIO_PinAFConfig(GPIOE, GPIO_PinSource5, GPIO_AF14);
    GPIO_InitStructure.GPIO_Pin   = GPIO_Pin_5;
    GPIO_InitStructure.GPIO_Speed = GPIO_Speed_Very_High;
    GPIO_InitStructure.GPIO_Mode  = GPIO_Mode_AF_PP;
    GPIO_Init(GPIOE, &GPIO_InitStructure);

    // G[1] PE6(AF14)
    GPIO_PinAFConfig(GPIOE, GPIO_PinSource6, GPIO_AF14);
    GPIO_InitStructure.GPIO_Pin   = GPIO_Pin_6;
    GPIO_InitStructure.GPIO_Speed = GPIO_Speed_Very_High;
    GPIO_InitStructure.GPIO_Mode  = GPIO_Mode_AF_PP;
    GPIO_Init(GPIOE, &GPIO_InitStructure);

    // G[2] PA6(AF14)
    GPIO_PinAFConfig(GPIOA, GPIO_PinSource6, GPIO_AF14);
    GPIO_InitStructure.GPIO_Pin   = GPIO_Pin_6;
    GPIO_InitStructure.GPIO_Speed = GPIO_Speed_Very_High;
    GPIO_InitStructure.GPIO_Mode  = GPIO_Mode_AF_PP;
    GPIO_Init(GPIOA, &GPIO_InitStructure);

    // G[3] PC9(AF10)
    GPIO_PinAFConfig(GPIOC, GPIO_PinSource9, GPIO_AF10);
    GPIO_InitStructure.GPIO_Pin   = GPIO_Pin_9;
    GPIO_InitStructure.GPIO_Speed = GPIO_Speed_Very_High;
    GPIO_InitStructure.GPIO_Mode  = GPIO_Mode_AF_PP;
    GPIO_Init(GPIOC, &GPIO_InitStructure);

    // G[4] PC8(AF14)
    GPIO_PinAFConfig(GPIOC, GPIO_PinSource8, GPIO_AF14);
    GPIO_InitStructure.GPIO_Pin   = GPIO_Pin_8;
    GPIO_InitStructure.GPIO_Speed = GPIO_Speed_Very_High;
    GPIO_InitStructure.GPIO_Mode  = GPIO_Mode_AF_PP;
    GPIO_Init(GPIOC, &GPIO_InitStructure);

    // G[5] PC1(AF14)
    GPIO_PinAFConfig(GPIOC, GPIO_PinSource1, GPIO_AF14);
    GPIO_InitStructure.GPIO_Pin   = GPIO_Pin_1;
    GPIO_InitStructure.GPIO_Speed = GPIO_Speed_Very_High;
    GPIO_InitStructure.GPIO_Mode  = GPIO_Mode_AF_PP;
    GPIO_Init(GPIOC, &GPIO_InitStructure);

    // G[6] PC7(AF14)
    GPIO_PinAFConfig(GPIOC, GPIO_PinSource7, GPIO_AF14);
    GPIO_InitStructure.GPIO_Pin   = GPIO_Pin_7;
    GPIO_InitStructure.GPIO_Speed = GPIO_Speed_Very_High;
    GPIO_InitStructure.GPIO_Mode  = GPIO_Mode_AF_PP;
    GPIO_Init(GPIOC, &GPIO_InitStructure);

    // G[7] PD3(AF14)
    GPIO_PinAFConfig(GPIOD, GPIO_PinSource3, GPIO_AF14);
    GPIO_InitStructure.GPIO_Pin   = GPIO_Pin_3;
    GPIO_InitStructure.GPIO_Speed = GPIO_Speed_Very_High;
    GPIO_InitStructure.GPIO_Mode  = GPIO_Mode_AF_PP;
    GPIO_Init(GPIOD, &GPIO_InitStructure);

    // B[0] PE4(AF14)
    GPIO_PinAFConfig(GPIOE, GPIO_PinSource4, GPIO_AF14);
    GPIO_InitStructure.GPIO_Pin   = GPIO_Pin_4;
    GPIO_InitStructure.GPIO_Speed = GPIO_Speed_Very_High;
    GPIO_InitStructure.GPIO_Mode  = GPIO_Mode_AF_PP;
    GPIO_Init(GPIOE, &GPIO_InitStructure);

    // B[1] PE0(AF14)
    GPIO_PinAFConfig(GPIOE, GPIO_PinSource0, GPIO_AF14);
    GPIO_InitStructure.GPIO_Pin   = GPIO_Pin_0;
    GPIO_InitStructure.GPIO_Speed = GPIO_Speed_Very_High;
    GPIO_InitStructure.GPIO_Mode  = GPIO_Mode_AF_PP;
    GPIO_Init(GPIOE, &GPIO_InitStructure);

    // B[2] PD6(AF14)
    GPIO_PinAFConfig(GPIOD, GPIO_PinSource6, GPIO_AF14);
    GPIO_InitStructure.GPIO_Pin   = GPIO_Pin_6;
    GPIO_InitStructure.GPIO_Speed = GPIO_Speed_Very_High;
    GPIO_InitStructure.GPIO_Mode  = GPIO_Mode_AF_PP;
    GPIO_Init(GPIOD, &GPIO_InitStructure);

    // B[3] PD7(AF14)
    GPIO_PinAFConfig(GPIOD, GPIO_PinSource7, GPIO_AF14);
    GPIO_InitStructure.GPIO_Pin   = GPIO_Pin_7;
    GPIO_InitStructure.GPIO_Speed = GPIO_Speed_Very_High;
    GPIO_InitStructure.GPIO_Mode  = GPIO_Mode_AF_PP;
    GPIO_Init(GPIOD, &GPIO_InitStructure);

    // B[4] PD4(AF14)
    GPIO_PinAFConfig(GPIOD, GPIO_PinSource4, GPIO_AF14);
    GPIO_InitStructure.GPIO_Pin   = GPIO_Pin_4;
    GPIO_InitStructure.GPIO_Speed = GPIO_Speed_Very_High;
    GPIO_InitStructure.GPIO_Mode  = GPIO_Mode_AF_PP;
    GPIO_Init(GPIOD, &GPIO_InitStructure);

    // B[5] PD5(AF14)
    GPIO_PinAFConfig(GPIOD, GPIO_PinSource5, GPIO_AF14);
    GPIO_InitStructure.GPIO_Pin   = GPIO_Pin_5;
    GPIO_InitStructure.GPIO_Speed = GPIO_Speed_Very_High;
    GPIO_InitStructure.GPIO_Mode  = GPIO_Mode_AF_PP;
    GPIO_Init(GPIOD, &GPIO_InitStructure);

    // B[6] PA14(AF14)
    GPIO_PinAFConfig(GPIOA, GPIO_PinSource14, GPIO_AF14);
    GPIO_InitStructure.GPIO_Pin   = GPIO_Pin_14;
    GPIO_InitStructure.GPIO_Speed = GPIO_Speed_Very_High;
    GPIO_InitStructure.GPIO_Mode  = GPIO_Mode_AF_PP;
    GPIO_Init(GPIOA, &GPIO_InitStructure);

    // B[7] PD2(AF9)
    GPIO_PinAFConfig(GPIOD, GPIO_PinSource2, GPIO_AF9);
    GPIO_InitStructure.GPIO_Pin   = GPIO_Pin_2;
    GPIO_InitStructure.GPIO_Speed = GPIO_Speed_Very_High;
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
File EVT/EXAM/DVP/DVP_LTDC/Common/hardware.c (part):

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    RCC_HB2PeriphClockCmd(RCC_HB2Periph_GPIOE, ENABLE);
    RCC_HB2PeriphClockCmd(RCC_HB2Periph_GPIOF, ENABLE);

    // CLK PF1(AF14)
    GPIO_PinAFConfig(GPIOF, GPIO_PinSource1, GPIO_AF14);
    GPIO_InitStructure.GPIO_Pin = GPIO_Pin_1;
    GPIO_InitStructure.GPIO_Speed = GPIO_Speed_Very_High;
    GPIO_InitStructure.GPIO_Mode = GPIO_Mode_AF_PP;
    GPIO_Init(GPIOF, &GPIO_InitStructure);

    // HSYNC PC10(AF15)
    GPIO_PinAFConfig(GPIOC, GPIO_PinSource10, GPIO_AF15);
    GPIO_InitStructure.GPIO_Pin = GPIO_Pin_10;
    GPIO_InitStructure.GPIO_Speed = GPIO_Speed_Very_High;
    GPIO_InitStructure.GPIO_Mode = GPIO_Mode_AF_PP;
    GPIO_Init(GPIOC, &GPIO_InitStructure);

    // VSYNC PC11(AF15)
    GPIO_PinAFConfig(GPIOC, GPIO_PinSource11, GPIO_AF15);
    GPIO_InitStructure.GPIO_Pin = GPIO_Pin_11;
    GPIO_InitStructure.GPIO_Speed = GPIO_Speed_Very_High;
    GPIO_InitStructure.GPIO_Mode = GPIO_Mode_AF_PP;
    GPIO_Init(GPIOC, &GPIO_InitStructure);

    // DE PC5(AF14)
    GPIO_PinAFConfig(GPIOC, GPIO_PinSource5, GPIO_AF14);
    GPIO_InitStructure.GPIO_Pin = GPIO_Pin_5;
    GPIO_InitStructure.GPIO_Speed = GPIO_Speed_Very_High;
    GPIO_InitStructure.GPIO_Mode = GPIO_Mode_AF_PP;
    GPIO_Init(GPIOC, &GPIO_InitStructure);

    // R[3] PD0(AF15)
    GPIO_PinAFConfig(GPIOD, GPIO_PinSource0, GPIO_AF15);
    GPIO_InitStructure.GPIO_Pin = GPIO_Pin_0;
    GPIO_InitStructure.GPIO_Speed = GPIO_Speed_Very_High;
    GPIO_InitStructure.GPIO_Mode = GPIO_Mode_AF_PP;
    GPIO_Init(GPIOD, &GPIO_InitStructure);

    // R[4] PA5(AF14)
    GPIO_PinAFConfig(GPIOA, GPIO_PinSource5, GPIO_AF14);
    GPIO_InitStructure.GPIO_Pin = GPIO_Pin_5;
    GPIO_InitStructure.GPIO_Speed = GPIO_Speed_Very_High;
    GPIO_InitStructure.GPIO_Mode = GPIO_Mode_AF_PP;
    GPIO_Init(GPIOA, &GPIO_InitStructure);

    // R[5] PA9(AF14)
    GPIO_PinAFConfig(GPIOA, GPIO_PinSource9, GPIO_AF14);
    GPIO_InitStructure.GPIO_Pin = GPIO_Pin_9;
    GPIO_InitStructure.GPIO_Speed = GPIO_Speed_Very_High;
    GPIO_InitStructure.GPIO_Mode = GPIO_Mode_AF_PP;
    GPIO_Init(GPIOA, &GPIO_InitStructure);

    // R[6] PA8(AF14)
    GPIO_PinAFConfig(GPIOA, GPIO_PinSource8, GPIO_AF14);
    GPIO_InitStructure.GPIO_Pin = GPIO_Pin_8;
    GPIO_InitStructure.GPIO_Speed = GPIO_Speed_Very_High;
    GPIO_InitStructure.GPIO_Mode = GPIO_Mode_AF_PP;
    GPIO_Init(GPIOA, &GPIO_InitStructure);

    // R[7] PD4(AF15)
    GPIO_PinAFConfig(GPIOD, GPIO_PinSource4, GPIO_AF15);
    GPIO_InitStructure.GPIO_Pin = GPIO_Pin_4;
    GPIO_InitStructure.GPIO_Speed = GPIO_Speed_Very_High;
    GPIO_InitStructure.GPIO_Mode = GPIO_Mode_AF_PP;
    GPIO_Init(GPIOD, &GPIO_InitStructure);

    // G[2] PA6(AF14)
    GPIO_PinAFConfig(GPIOA, GPIO_PinSource6, GPIO_AF14);
    GPIO_InitStructure.GPIO_Pin = GPIO_Pin_6;
    GPIO_InitStructure.GPIO_Speed = GPIO_Speed_Very_High;
    GPIO_InitStructure.GPIO_Mode = GPIO_Mode_AF_PP;
    GPIO_Init(GPIOA, &GPIO_InitStructure);

    // G[3] PD6(AF15)
    GPIO_PinAFConfig(GPIOD, GPIO_PinSource6, GPIO_AF15);
    GPIO_InitStructure.GPIO_Pin = GPIO_Pin_6;
    GPIO_InitStructure.GPIO_Speed = GPIO_Speed_Very_High;
    GPIO_InitStructure.GPIO_Mode = GPIO_Mode_AF_PP;
    GPIO_Init(GPIOD, &GPIO_InitStructure);

    // G[4] PB10(AF14)
    GPIO_PinAFConfig(GPIOB, GPIO_PinSource10, GPIO_AF14);
    GPIO_InitStructure.GPIO_Pin = GPIO_Pin_10;
    GPIO_InitStructure.GPIO_Speed = GPIO_Speed_Very_High;
    GPIO_InitStructure.GPIO_Mode = GPIO_Mode_AF_PP;
    GPIO_Init(GPIOB, &GPIO_InitStructure);

    // G[5] PC1(AF14)
    GPIO_PinAFConfig(GPIOC, GPIO_PinSource1, GPIO_AF14);
    GPIO_InitStructure.GPIO_Pin = GPIO_Pin_1;
    GPIO_InitStructure.GPIO_Speed = GPIO_Speed_Very_High;
    GPIO_InitStructure.GPIO_Mode = GPIO_Mode_AF_PP;
    GPIO_Init(GPIOC, &GPIO_InitStructure);

    // G[6] PF4(AF15)
    GPIO_PinAFConfig(GPIOF, GPIO_PinSource4, GPIO_AF15);
    GPIO_InitStructure.GPIO_Pin = GPIO_Pin_4;
    GPIO_InitStructure.GPIO_Speed = GPIO_Speed_Very_High;
    GPIO_InitStructure.GPIO_Mode = GPIO_Mode_AF_PP;
    GPIO_Init(GPIOF, &GPIO_InitStructure);

    // G[7] PB15(AF14)
    GPIO_PinAFConfig(GPIOB, GPIO_PinSource15, GPIO_AF14);
    GPIO_InitStructure.GPIO_Pin = GPIO_Pin_15;
    GPIO_InitStructure.GPIO_Speed = GPIO_Speed_Very_High;
    GPIO_InitStructure.GPIO_Mode = GPIO_Mode_AF_PP;
    GPIO_Init(GPIOB, &GPIO_InitStructure);

    // B[3] PD7(AF14)
    GPIO_PinAFConfig(GPIOD, GPIO_PinSource7, GPIO_AF14);
    GPIO_InitStructure.GPIO_Pin = GPIO_Pin_7;
    GPIO_InitStructure.GPIO_Speed = GPIO_Speed_Very_High;
    GPIO_InitStructure.GPIO_Mode = GPIO_Mode_AF_PP;
    GPIO_Init(GPIOD, &GPIO_InitStructure);

    // B[4] PE0(AF9)
    GPIO_PinAFConfig(GPIOE, GPIO_PinSource0, GPIO_AF9);
    GPIO_InitStructure.GPIO_Pin = GPIO_Pin_0;
    GPIO_InitStructure.GPIO_Speed = GPIO_Speed_Very_High;
    GPIO_InitStructure.GPIO_Mode = GPIO_Mode_AF_PP;
    GPIO_Init(GPIOE, &GPIO_InitStructure);

    // B[5] PA3(AF14)
    GPIO_PinAFConfig(GPIOA, GPIO_PinSource3, GPIO_AF14);
    GPIO_InitStructure.GPIO_Pin = GPIO_Pin_3;
    GPIO_InitStructure.GPIO_Speed = GPIO_Speed_Very_High;
    GPIO_InitStructure.GPIO_Mode = GPIO_Mode_AF_PP;
    GPIO_Init(GPIOA, &GPIO_InitStructure);

    // B[6] PA15(AF14)
    GPIO_PinAFConfig(GPIOA, GPIO_PinSource15, GPIO_AF14);
    GPIO_InitStructure.GPIO_Pin = GPIO_Pin_15;
    GPIO_InitStructure.GPIO_Speed = GPIO_Speed_Very_High;
    GPIO_InitStructure.GPIO_Mode = GPIO_Mode_AF_PP;
    GPIO_Init(GPIOA, &GPIO_InitStructure);

    // B[7] PD2(AF9)
    GPIO_PinAFConfig(GPIOD, GPIO_PinSource2, GPIO_AF9);
    GPIO_InitStructure.GPIO_Pin = GPIO_Pin_2;
    GPIO_InitStructure.GPIO_Speed = GPIO_Speed_Very_High;
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
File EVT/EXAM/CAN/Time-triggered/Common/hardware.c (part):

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
/**
 * @brief  CAN Tx pin table
 * @note   CAN1: PA12, PB7, PB9, PD1, PA14
 *         CAN2: PB13, PB6
 *         CAN3: PD13, PF7, PF3, PC5
 */
const CANPinTable_t CANTXPinTable[] = {
    {CAN1, GPIOA, 12, GPIO_AF9}, {CAN1, GPIOB, 7, GPIO_AF3}, {CAN1, GPIOB, 9, GPIO_AF9}, {CAN1, GPIOD, 1, GPIO_AF9},
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};
/**
 * @brief  CAN Rx pin table
 * @note   CAN1: PA11, PB6, PB8, PD0, PA13
 *         CAN2: PB12, PB5
 *         CAN3: PD12, PF6, PF4, PC4
 */
const CANPinTable_t CANRXPinTable[] = {
    {CAN1, GPIOA, 11, GPIO_AF9}, {CAN1, GPIOB, 6, GPIO_AF3}, {CAN1, GPIOB, 8, GPIO_AF9}, {CAN1, GPIOD, 0, GPIO_AF9},
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
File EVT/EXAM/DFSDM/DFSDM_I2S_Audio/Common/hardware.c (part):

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    GPIO_InitTypeDef GPIO_InitStructure = {0};
    RCC_HB2PeriphClockCmd(RCC_HB2Periph_GPIOB | RCC_HB2Periph_GPIOC, ENABLE);

    /* Config DFSDM_CKOUT(PC2) -- DFSDM_DATIN1(PC3)  */
    GPIO_PinAFConfig(GPIOC, GPIO_PinSource2, GPIO_AF6); 
    GPIO_PinAFConfig(GPIOC, GPIO_PinSource3, GPIO_AF3);

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    GPIO_InitStructure.GPIO_Mode = GPIO_Mode_IN_FLOATING;
    GPIO_Init(GPIOC, &GPIO_InitStructure);
    
    /* WS PB12(AF5) */
    GPIO_PinAFConfig(GPIOB, GPIO_PinSource12, GPIO_AF5);
    GPIO_InitStructure.GPIO_Pin   = GPIO_Pin_12;
    GPIO_InitStructure.GPIO_Speed = GPIO_Speed_Very_High;
    GPIO_InitStructure.GPIO_Mode  = GPIO_Mode_AF_PP;
    GPIO_Init(GPIOB, &GPIO_InitStructure);

    /* CK PB13(AF5) */
    GPIO_PinAFConfig(GPIOB, GPIO_PinSource13, GPIO_AF5);
    GPIO_InitStructure.GPIO_Pin   = GPIO_Pin_13;
    GPIO_InitStructure.GPIO_Speed = GPIO_Speed_Very_High;
    GPIO_InitStructure.GPIO_Mode  = GPIO_Mode_AF_PP;
    GPIO_Init(GPIOB, &GPIO_InitStructure);

    /* SD PC1(AF5) */
    GPIO_PinAFConfig(GPIOC, GPIO_PinSource1, GPIO_AF5);
    GPIO_InitStructure.GPIO_Pin   = GPIO_Pin_1;
    GPIO_InitStructure.GPIO_Speed = GPIO_Speed_Very_High;
    GPIO_InitStructure.GPIO_Mode  = GPIO_Mode_AF_PP;
    GPIO_Init(GPIOC, &GPIO_InitStructure);
      
    /* MCK PC6(AF5) */
    GPIO_PinAFConfig(GPIOC, GPIO_PinSource6, GPIO_AF5);
    GPIO_InitStructure.GPIO_Pin   = GPIO_Pin_6;
    GPIO_InitStructure.GPIO_Speed = GPIO_Speed_Very_High;
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
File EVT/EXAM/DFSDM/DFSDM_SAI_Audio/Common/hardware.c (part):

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    GPIO_InitTypeDef GPIO_InitStructure = {0};
    RCC_HB2PeriphClockCmd(RCC_HB2Periph_GPIOB | RCC_HB2Periph_GPIOC | RCC_HB2Periph_GPIOE, ENABLE);

    /* Config DFSDM_CKOUT(PB0) -- DFSDM_DATIN1(PB12)  */
    GPIO_PinAFConfig(GPIOB, GPIO_PinSource0, GPIO_AF6); 
    GPIO_PinAFConfig(GPIOB, GPIO_PinSource12, GPIO_AF6);

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    GPIO_InitStructure.GPIO_Mode = GPIO_Mode_IN_FLOATING;
    GPIO_Init(GPIOB, &GPIO_InitStructure);
    
    // SAI_FS_A PC3(AF7)
    GPIO_PinAFConfig(GPIOC, GPIO_PinSource3, GPIO_AF7);
    GPIO_InitStructure.GPIO_Pin   = GPIO_Pin_3;
    GPIO_InitStructure.GPIO_Speed = GPIO_Speed_High;
    GPIO_InitStructure.GPIO_Mode  = GPIO_Mode_AF_PP;
    GPIO_Init(GPIOC, &GPIO_InitStructure);

    // SAI_SCK_A PC2(AF7)
    GPIO_PinAFConfig(GPIOC, GPIO_PinSource2, GPIO_AF7);
    GPIO_InitStructure.GPIO_Pin   = GPIO_Pin_2;
    GPIO_InitStructure.GPIO_Speed = GPIO_Speed_High;
    GPIO_InitStructure.GPIO_Mode  = GPIO_Mode_AF_PP;
    GPIO_Init(GPIOC, &GPIO_InitStructure);

    // SAI_SD_A PB2(AF6)
    GPIO_PinAFConfig(GPIOB, GPIO_PinSource2, GPIO_AF6);
    GPIO_InitStructure.GPIO_Pin   = GPIO_Pin_2;
    GPIO_InitStructure.GPIO_Speed = GPIO_Speed_High;
    GPIO_InitStructure.GPIO_Mode  = GPIO_Mode_AF_PP;
    GPIO_Init(GPIOB, &GPIO_InitStructure);

    // SAI_MCLK_A PE2(AF6)
    GPIO_PinAFConfig(GPIOE, GPIO_PinSource2, GPIO_AF6);
    GPIO_InitStructure.GPIO_Pin   = GPIO_Pin_2;
    GPIO_InitStructure.GPIO_Speed = GPIO_Speed_High;
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
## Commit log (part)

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2025-08-06 init
2026-06-15 update update.sh and add GitHub Actions workflow for automated datasheet downloads
2026-06-15 refactor update job to simplify commit logic in GitHub Actions workflow
2026-06-16 update GitHub Actions schedule
2026-06-19 update GitHub Actions workflow to implement keepalive logic and remove unnecessary permissions
2026-06-19 refactor fetch function in update.sh to simplify error handling and remove retry logic

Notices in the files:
EVT/EXAM/APPLICATION/LTDC_LVGL/Common/hardware.c:
Copyright (c) 2025 Nanjing Qinheng Microelectronics Co., Ltd.
